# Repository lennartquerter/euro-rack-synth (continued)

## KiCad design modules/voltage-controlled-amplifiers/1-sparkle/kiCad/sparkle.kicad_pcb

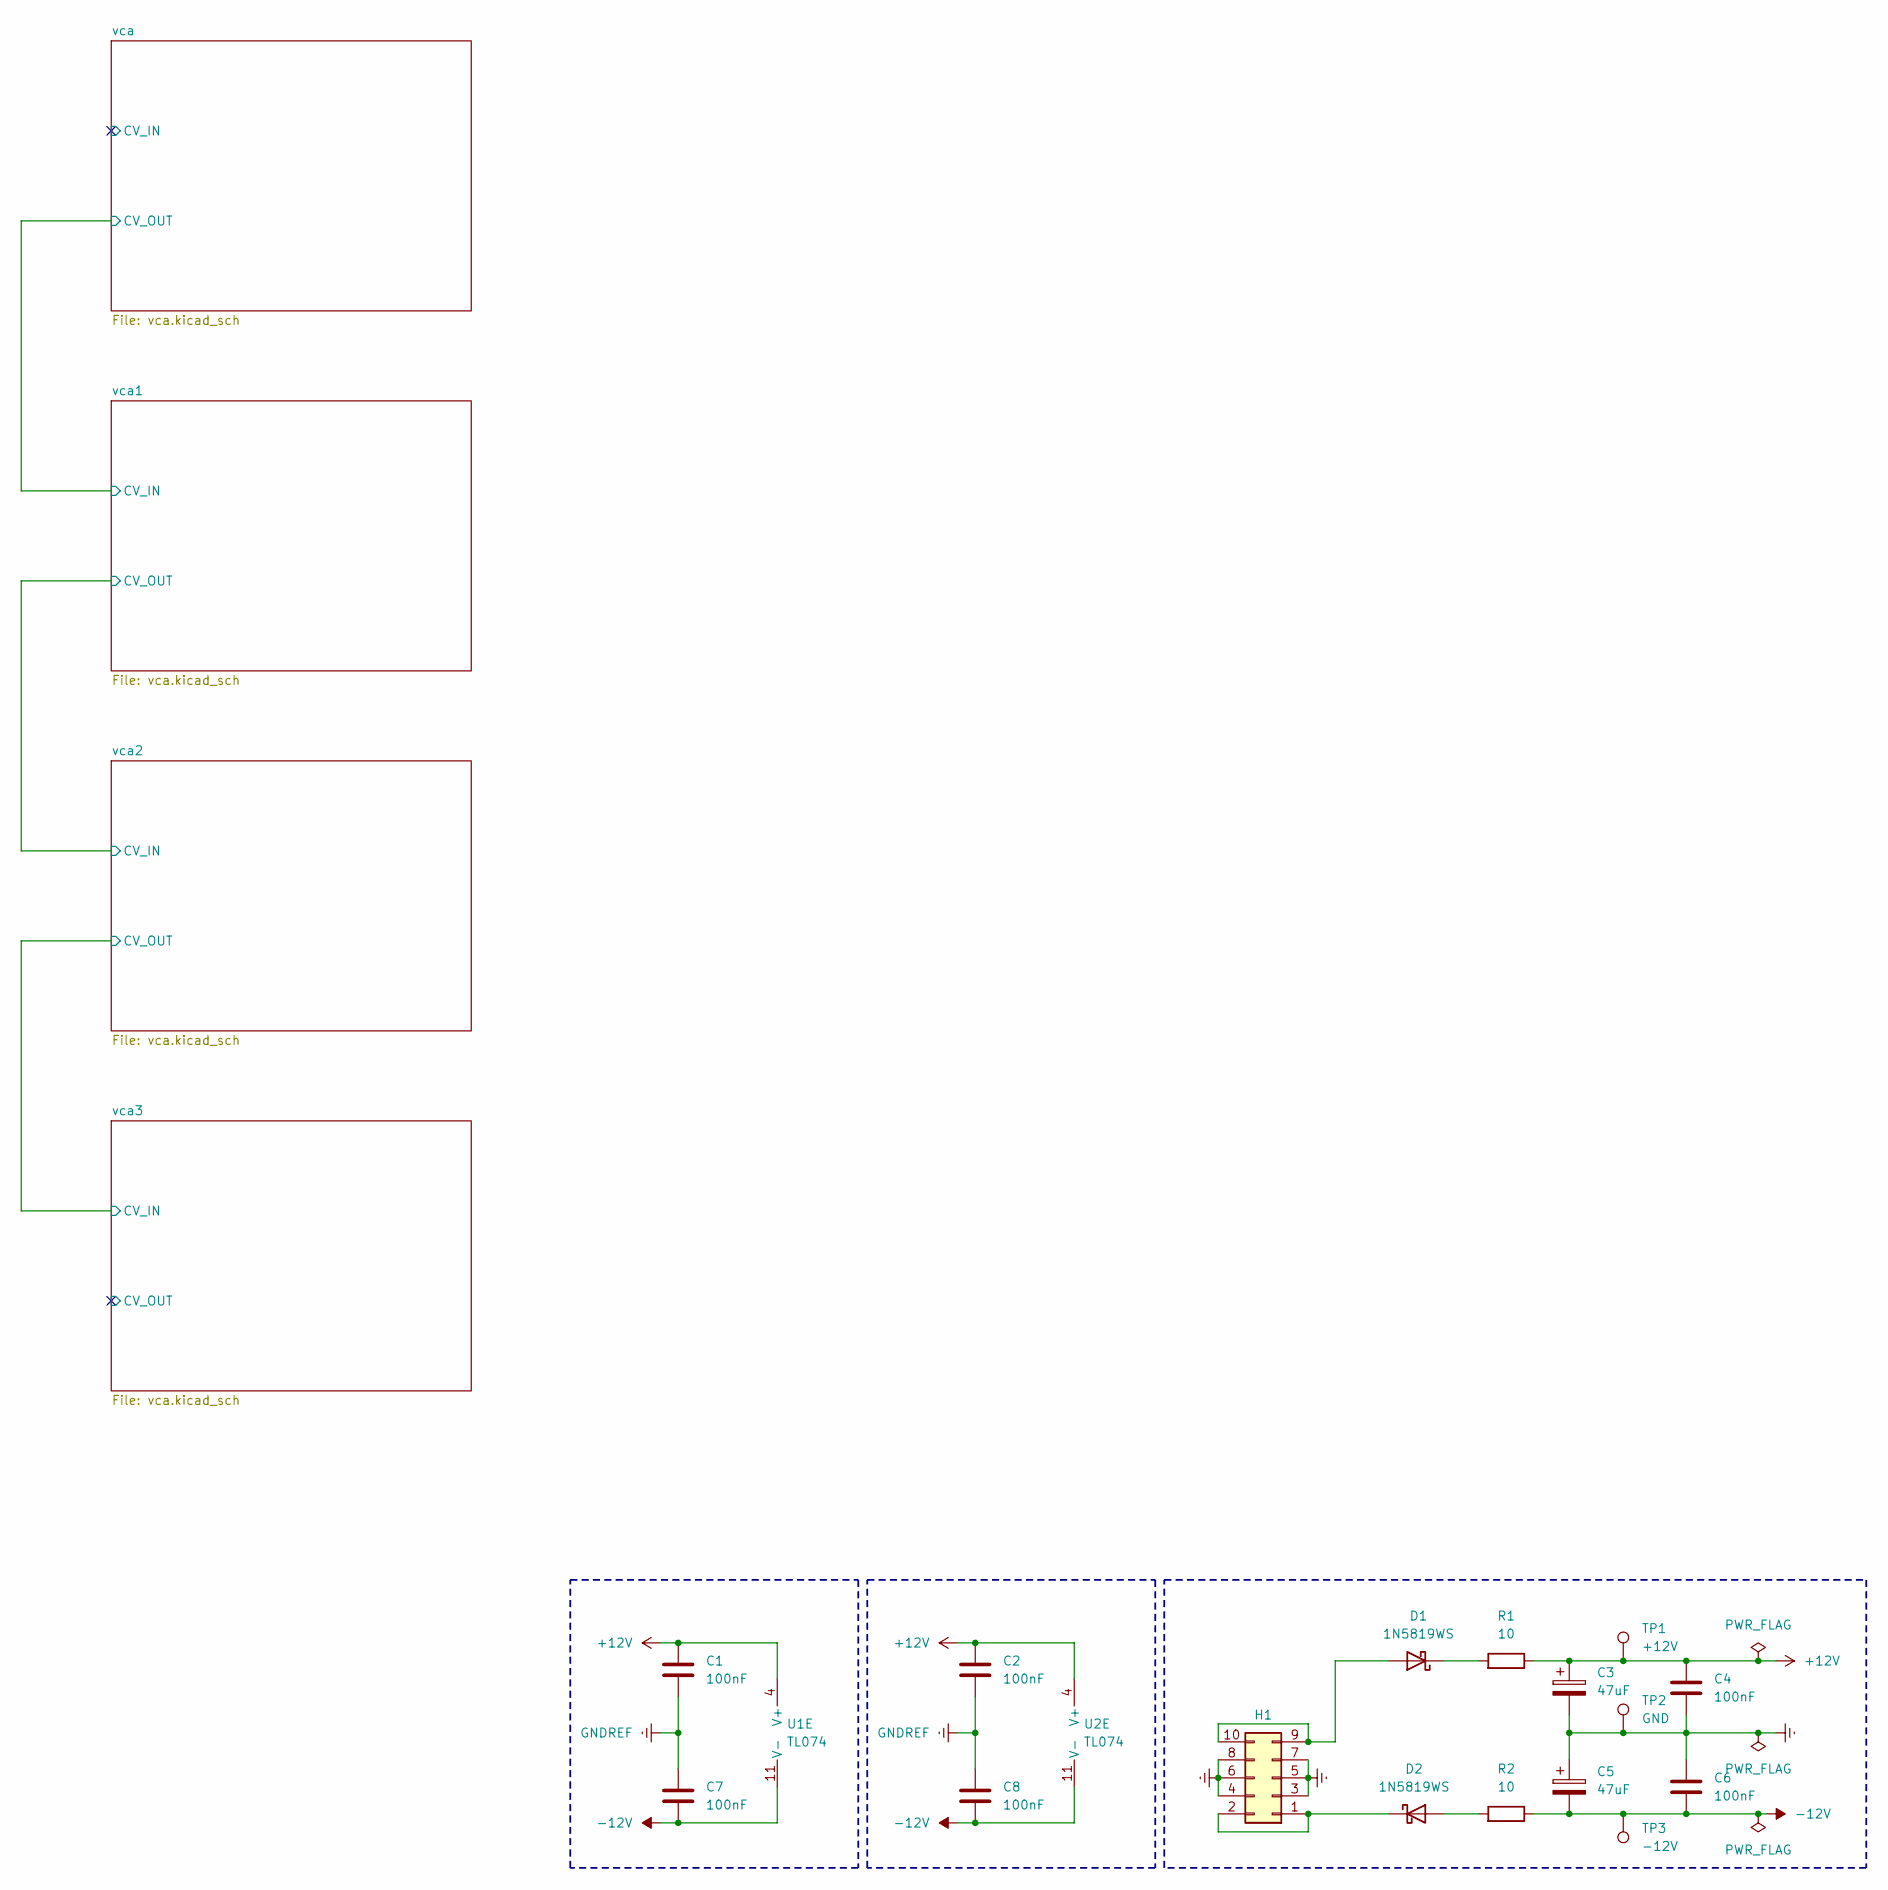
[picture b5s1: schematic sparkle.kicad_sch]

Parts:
C1, C2, C4, C6, C7, C8: 100nF; C_0805_2012Metric_Pad1.18x1.45mm_HandSolder
C3, C5: 47uF; CP_Radial_D6.3mm_P2.50mm
D1, D2: 1N5819WS; D_SOD-323_HandSoldering
H1: Conn_02x05_PWR_Eurorack; IDC-Header_2x05_P2.54mm_Vertical
R1, R2: 10; R_0805_2012Metric_Pad1.20x1.40mm_HandSolder
TP1: +12V; Pin_D1.0mm_L10.0mm
TP2: GND; Pin_D1.0mm_L10.0mm
TP3: -12V; Pin_D1.0mm_L10.0mm
U1, U2: TL074; SOIC-14

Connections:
+12V: C1.1, C2.1, C3.1, C4.1, R1.2, TP1.1, U1.4 (V+), U2.4 (V+); also elsewhere on the board
-12V: C5.2, C6.2, C7.2, C8.2, R2.2, TP3.1, U1.11 (V-), U2.11 (V-); also elsewhere on the board
GNDREF: C1.2, C2.2, C3.2, C4.2, C5.1, C6.1, C7.1, C8.1, H1.3, H1.4, H1.5, H1.6, H1.7, H1.8, TP2.1, U1.5 (+), U2.5 (+); also elsewhere on the board
unnamed: D1.2 (A), H1.9, H1.10
unnamed: D1.1 (K), R1.1
unnamed: D2.2 (A), R2.1
unnamed: D2.1 (K), H1.1, H1.2
unnamed 45: U1.8; also elsewhere on the board
unnamed 49: U1.7; also elsewhere on the board
unnamed 54: U2.7; also elsewhere on the board
unnamed 55: U2.8; also elsewhere on the board
unnamed 61: U1.6 (-); also elsewhere on the board
unnamed 62: U1.10 (+); also elsewhere on the board
unnamed 63: U1.9 (-); also elsewhere on the board
unnamed 68: U2.6 (-); also elsewhere on the board
unnamed 69: U2.10 (+); also elsewhere on the board
unnamed 70: U2.9 (-); also elsewhere on the board

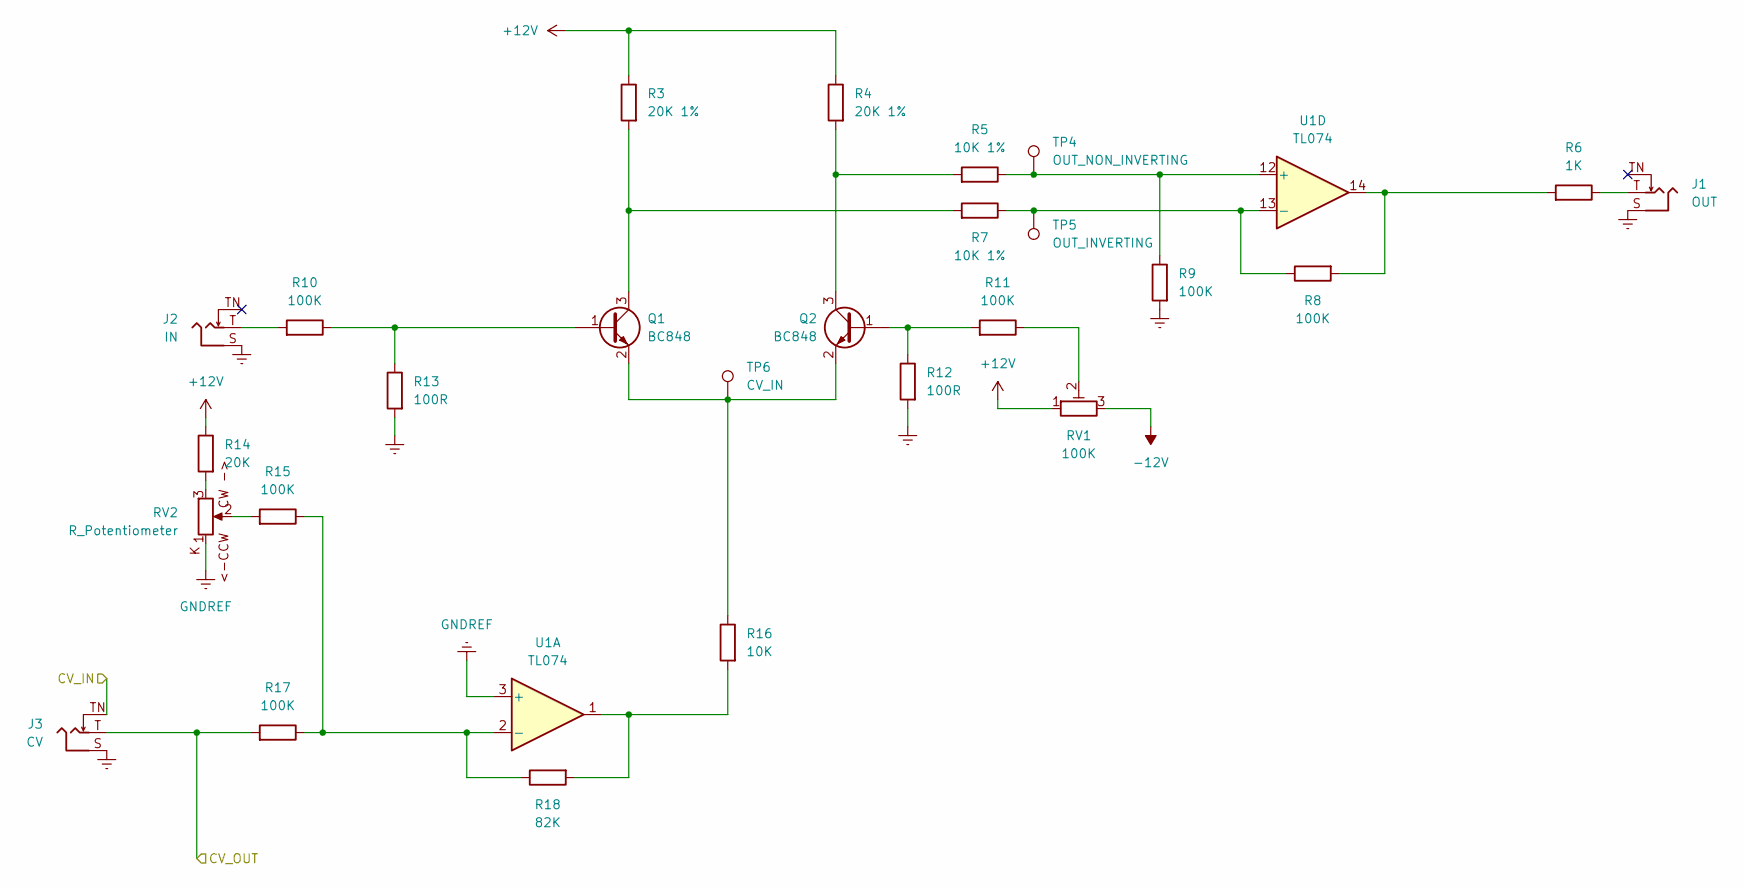
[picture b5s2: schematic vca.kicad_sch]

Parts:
J1: OUT; Jack_3.5mm_QingPu_WQP-PJ398SM_Vertical_CircularHoles
J2: IN; Jack_3.5mm_QingPu_WQP-PJ398SM_Vertical_CircularHoles
J3: CV; Jack_3.5mm_QingPu_WQP-PJ398SM_Vertical_CircularHoles
Q1, Q2: BC848; SOT-23_Handsoldering
R3, R4: 20K 1%; R_0805_2012Metric_Pad1.20x1.40mm_HandSolder
R5, R7: 10K 1%; R_0805_2012Metric_Pad1.20x1.40mm_HandSolder
R6: 1K; R_0805_2012Metric_Pad1.20x1.40mm_HandSolder
R8, R9, R10, R11, R15, R17: 100K; R_0805_2012Metric_Pad1.20x1.40mm_HandSolder
R12, R13: 100R; R_0805_2012Metric_Pad1.20x1.40mm_HandSolder
R14: 20K; R_0805_2012Metric_Pad1.20x1.40mm_HandSolder
R16: 10K; R_0805_2012Metric_Pad1.20x1.40mm_HandSolder
R18: 82K; R_0805_2012Metric_Pad1.20x1.40mm_HandSolder
RV1: 100K; Potentiometer_SMD_23BRXXKLRTR
RV2: R_Potentiometer; Potentiometer_TT_P0915N
TP4: OUT_NON_INVERTING; Pin_D1.0mm_L10.0mm
TP5: OUT_INVERTING; Pin_D1.0mm_L10.0mm
TP6: CV_IN; Pin_D1.0mm_L10.0mm
U1: TL074; SOIC-14

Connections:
+12V: R3.2, R4.2, R14.2, RV1.1; also elsewhere on the board
-12V: RV1.3; also elsewhere on the board
/vca/CV_IN: J3.TN
/vca/CV_OUT: J3.T, R17.1; also elsewhere on the board
GNDREF: J1.S, J2.S, J3.S, R9.1, R12.1, R13.1, RV2.1, U1.3 (+), U1.5 (+); also elsewhere on the board
unnamed: J1.T, R6.2
unnamed: J2.T, R10.1
unnamed: Q1.1 (B), R10.2, R13.2
unnamed: Q1.3 (C), R3.1, R7.1
unnamed: Q1.2 (E), Q2.2 (E), R16.2, TP6.1
unnamed: Q2.1 (B), R11.1, R12.2
unnamed: Q2.3 (C), R4.1, R5.1
unnamed: R6.1, R8.1, U1.14
unnamed: R11.2, RV1.2
unnamed: R14.1, RV2.3
unnamed: R15.1, RV2.2
unnamed: R16.1, R18.1, U1.1
unnamed 45: U1.8; also elsewhere on the board
unnamed 49: U1.7; also elsewhere on the board
unnamed: R15.2, R17.2, R18.2, U1.2 (-)
unnamed 61: U1.6 (-); also elsewhere on the board
unnamed 62: U1.10 (+); also elsewhere on the board
unnamed 63: U1.9 (-); also elsewhere on the board
unnamed: R5.2, R9.2, TP4.1, U1.12 (+)
unnamed: R7.2, R8.2, TP5.1, U1.13 (-)

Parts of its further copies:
J4, J7, J10: OUT; Jack_3.5mm_QingPu_WQP-PJ398SM_Vertical_CircularHoles
J5, J8, J11: IN; Jack_3.5mm_QingPu_WQP-PJ398SM_Vertical_CircularHoles
J6, J9, J12: CV; Jack_3.5mm_QingPu_WQP-PJ398SM_Vertical_CircularHoles
Q3, Q4, Q5, Q6, Q7, Q8: BC848; SOT-23_Handsoldering
R19, R20, R35, R36, R51, R52: 20K 1%; R_0805_2012Metric_Pad1.20x1.40mm_HandSolder
R21, R23, R37, R39, R53, R55: 10K 1%; R_0805_2012Metric_Pad1.20x1.40mm_HandSolder
R22, R38, R54: 1K; R_0805_2012Metric_Pad1.20x1.40mm_HandSolder
R24, R25, R26, R27, R31, R33, R40, R41, R42, R43, R47, R49, R56, R57, R58, R59, R63, R65: 100K; R_0805_2012Metric_Pad1.20x1.40mm_HandSolder
R28, R29, R44, R45, R60, R61: 100R; R_0805_2012Metric_Pad1.20x1.40mm_HandSolder
R30, R46, R62: 20K; R_0805_2012Metric_Pad1.20x1.40mm_HandSolder
R32, R48, R64: 10K; R_0805_2012Metric_Pad1.20x1.40mm_HandSolder
R34, R50, R66: 82K; R_0805_2012Metric_Pad1.20x1.40mm_HandSolder
RV3, RV5, RV7: 100K; Potentiometer_SMD_23BRXXKLRTR
RV4, RV6, RV8: R_Potentiometer; Potentiometer_TT_P0915N
TP7, TP10, TP13: OUT_NON_INVERTING; Pin_D1.0mm_L10.0mm
TP8, TP11, TP14: OUT_INVERTING; Pin_D1.0mm_L10.0mm
TP9, TP12, TP15: CV_IN; Pin_D1.0mm_L10.0mm

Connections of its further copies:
+12V: R19.2, R20.2, R30.2, R35.2, R36.2, R46.2, R51.2, R52.2, R62.2, RV3.1, RV5.1, RV7.1; also elsewhere on the board
-12V: RV3.3, RV5.3, RV7.3; also elsewhere on the board
/vca1/CV_OUT: J6.T, J9.TN, R33.1
/vca2/CV_OUT: J9.T, J12.TN, R49.1
/vca3/CV_OUT: J12.T, R65.1
/vca/CV_OUT: J6.TN; also elsewhere on the board
GNDREF: J4.S, J5.S, J6.S, J7.S, J8.S, J9.S, J10.S, J11.S, J12.S, R25.1, R28.1, R29.1, R41.1, R44.1, R45.1, R57.1, R60.1, R61.1, RV4.1, RV6.1, RV8.1; also elsewhere on the board
unnamed: J4.T, R22.2
unnamed: J5.T, R26.1
unnamed: J7.T, R38.2
unnamed: J8.T, R42.1
unnamed: J10.T, R54.2
unnamed: J11.T, R58.1
unnamed: Q3.1 (B), R26.2, R29.2
unnamed: Q3.3 (C), R19.1, R23.1
unnamed: Q3.2 (E), Q4.2 (E), R32.2, TP9.1
unnamed: Q4.1 (B), R27.1, R28.2
unnamed: Q4.3 (C), R20.1, R21.1
unnamed: Q5.1 (B), R42.2, R45.2
unnamed: Q5.3 (C), R35.1, R39.1
unnamed: Q5.2 (E), Q6.2 (E), R48.2, TP12.1
unnamed: Q6.1 (B), R43.1, R44.2
unnamed: Q6.3 (C), R36.1, R37.1
unnamed: Q7.1 (B), R58.2, R61.2
unnamed: Q7.3 (C), R51.1, R55.1
unnamed: Q7.2 (E), Q8.2 (E), R64.2, TP15.1
unnamed: Q8.1 (B), R59.1, R60.2
unnamed: Q8.3 (C), R52.1, R53.1
unnamed 45: R22.1, R24.1; also elsewhere on the board
unnamed: R27.2, RV3.2
unnamed: R30.1, RV4.3
unnamed: R31.1, RV4.2
unnamed 49: R32.1, R34.1; also elsewhere on the board
unnamed 50: R38.1, R40.1; also elsewhere on the board
unnamed: R43.2, RV5.2
unnamed: R46.1, RV6.3
unnamed: R47.1, RV6.2
unnamed 54: R48.1, R50.1; also elsewhere on the board
unnamed 55: R54.1, R56.1; also elsewhere on the board
unnamed: R59.2, RV7.2
unnamed: R62.1, RV8.3
unnamed: R63.1, RV8.2
unnamed 59: R64.1, R66.1; also elsewhere on the board
unnamed 61: R31.2, R33.2, R34.2; also elsewhere on the board
unnamed 62: R21.2, R25.2, TP7.1; also elsewhere on the board
unnamed 63: R23.2, R24.2, TP8.1; also elsewhere on the board
unnamed 66: R37.2, R41.2, TP10.1; also elsewhere on the board
unnamed 67: R39.2, R40.2, TP11.1; also elsewhere on the board
unnamed 68: R47.2, R49.2, R50.2; also elsewhere on the board
unnamed 69: R53.2, R57.2, TP13.1; also elsewhere on the board
unnamed 70: R55.2, R56.2, TP14.1; also elsewhere on the board
unnamed 71: R63.2, R65.2, R66.2; also elsewhere on the board

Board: 2 copper layers, 122 parts (106 on the bottom side), 71 nets, no tracks yet.
